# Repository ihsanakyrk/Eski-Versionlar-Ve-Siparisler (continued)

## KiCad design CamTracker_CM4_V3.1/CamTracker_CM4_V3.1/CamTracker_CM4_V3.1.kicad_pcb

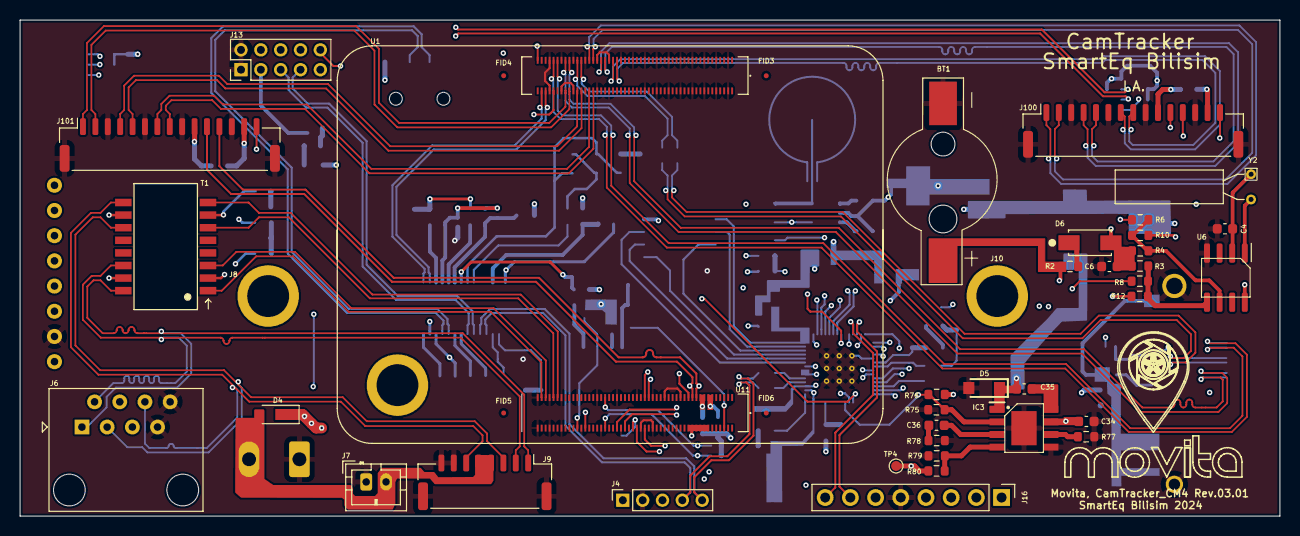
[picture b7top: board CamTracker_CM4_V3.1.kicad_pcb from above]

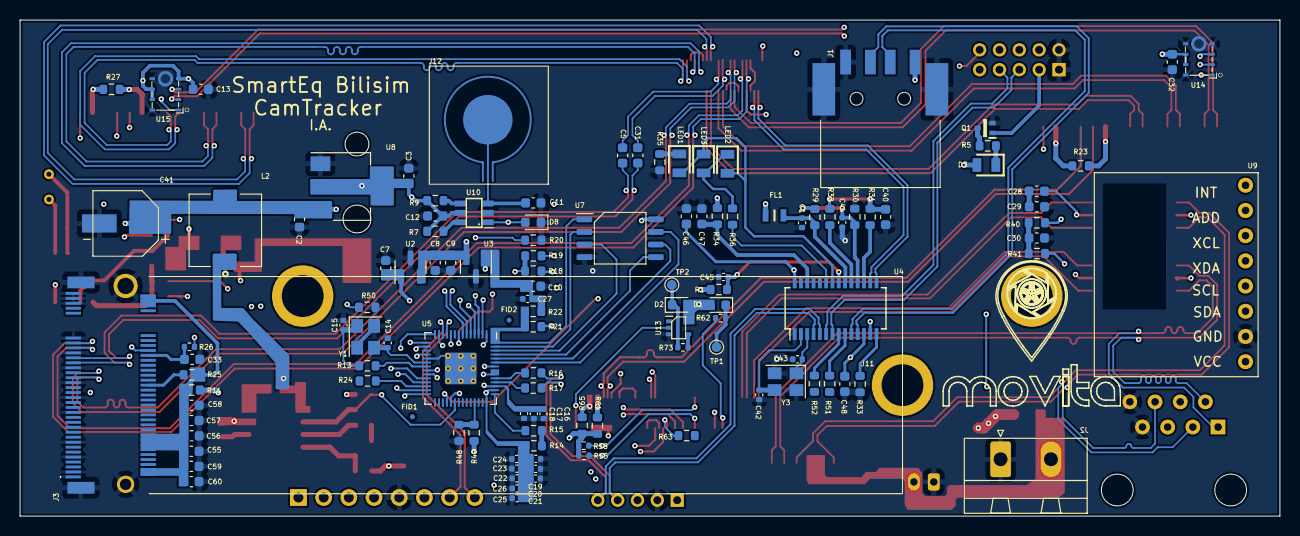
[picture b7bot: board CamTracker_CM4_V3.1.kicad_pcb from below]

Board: 6 copper layers, 127.0 x 50.0 mm, 163 parts (120 on the bottom side), 144 nets.

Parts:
BT1: MYOUNG MY-1220-01; BS-12-B3AA003
C1, C45: 10uF; C_0402_1005Metric
C2, C3, C7, C8, C9, C10, C34, C48: 10uF; C_0603_1608Metric
C4: 22pF; C_0603_1608Metric
C5, C31: 100nF X5R 10V; C_0603_1608Metric
C6, C35: 100nF; C_0603_1608Metric
C11: 30pF; C_0603_1608Metric
C12: 1uF; C_0603_1608Metric
C13, C32, C40, C46, C47, C55, C56, C57, C58, C59, C60: 0.1uF; C_0603_1608Metric
C14, C15, C42, C43: 27pF; C_0402_1005Metric
C16, C17, C20, C21, C22, C23, C24, C25, C26, C27: 100nF; C_0402_1005Metric
C18, C19: 1uF; C_0402_1005Metric
C28, C29: 0.01uF; C_0603_1608Metric
C30: 1000pF; C_0603_1608Metric
C33: 100nF X5R 16V; C_0603_1608Metric
C36: 150pF; C_0603_1608Metric
C41: 100uF; CAPAE660X550N
C44: 0.1uF; C_0402_1005Metric
D1: LED Green; LED_0603_1608Metric
D2: LED Red; LED_0603_1608Metric
D3: LED; LEDC2012X80N
D4: 2SS100L-W; 2SS100LW
D5: SS34FA; SODFL3618X143N
D6: SS14; DIOM4325X250N
D8: LED; LED_0603_1608Metric
FID1, FID2, FID3, FID4, FID5, FID6: Fiducial; Fiducial_0.5mm_Mask1mm
FL1: BLM21BB050SN1D; BLM21BB050SH1D
IC3: MP1584EN; SOIC127P600X170-9N
J1: USB-A Female SMD connector; USB_A_CNCTech_1001-011-01101_Horizontal
J2: DNP; PhoenixContact_MSTBA_2,5_2-G-5,08_1x02_P5.08mm_Horizontal
J3: APCI0079-P002A J8900 M.2 M Key; 121992306
J4: Conn_01x05_Male; PinSocket_1x05_P2.00mm_Vertical
J6: DNP; RJ45_Amphenol_54602-x08_Horizontal
J7: Conn_01x02_Female; JST_PH_B2B-PH-K_1x02_P2.00mm_Vertical
J8, J10: Screw_Terminal_01x01; Screw_terminal_shinbo
J9: JST_GH_BM08B-GHS-TBT_1x08-1MP_P1.25mm_Vertical
J11: M3x*0.5 L=3; Screw_terminal_shinbo
J12: DNP; Touch Pad
J13: MALE Through Hole PinHeader; PinHeader_2x05_P2.00mm_Vertical
J16: DNP; PinHeader_1x08_P2.54mm_Vertical
J100, J101: Conn_01x15_Female; JST_1x15-1MP_P1.25mm_Horizontal
L2: CDRH74NP-100MC-B; CDRH74NP100MCB
LED1, LED2, LED3: 150080VS75000; LEDC2012X80N
Q1: DTC043ZEBTL; SOTFL50P160X85-3N
R1, R7, R9, R10, R12, R19, R22, R50, R51, R52, R65: DNP; R_0603_1608Metric
R2: 150R; R_0603_1608Metric
R3, R4: 4.7K; R_0603_1608Metric
R5, R75: 2.2K; R_0603_1608Metric
R6, R8, R11, R18, R23, R24, R27, R63, R64: 0R; R_0603_1608Metric
R13, R21, R48: 1K; R_0603_1608Metric
R14: 200R; R_0603_1608Metric
R15: 1R; R_0603_1608Metric
R16, R17: 27R; R_0603_1608Metric
R20, R31, R32, R76, R78: 100K; R_0603_1608Metric
R25, R34, R49: 10K; R_0603_1608Metric
R26: 1K 5%; R_0402_1005Metric
R29, R30: 47K; R_0603_1608Metric
R33: 2.7K; R_0603_1608Metric
R35, R36: 470R; R_0603_1608Metric
R40, R41: 75R; R_0603_1608Metric
R55, R58: 2.2K 1%; R_0402_1005Metric
R62, R73: 1K; R_0402_1005Metric
R77: 200K; R_0603_1608Metric
R79: 40.2K; R_0603_1608Metric
R80: 210K; R_0603_1608Metric
T1: H1102NL
TP1, TP2, TP4: TestPoint; TestPoint_Pad_D1.0mm
U1: DF40C-100DS-0.4V; DF40C-100DS-0.4V_CM4_Unit_B
U2, U3: TLV76033DBZT; SOT-23
U4: FE1.1s; SSOP-28_3.9x9.9mm_P0.635mm
U5: RP2040; RP2040-QFN-56
U6: PCF8563T; SOIC-8_3.9x4.9mm_P1.27mm
U7: W25Q128JVS; SOIC-8_5.23x5.23mm_P1.27mm
U8: AMS1117-3.3; SOT-223-3_TabPin2
U9: DNP; module_mpu6050
U10: TTP223
U11: DF40C-100DS-0.4V; DF40C-100DS-0.4V_CM4_Unit_A
U13: 74LVC1G07SE-7; SOT-353_SC-70-5
U14, U15: INMP441
Y1, Y3: Crystal_GND12Mhz; Crystal_SMD_3225-4Pin_3.2x2.5mm
Y2: 32.768 KHz; Crystal_AT310_D3.0mm_L10.0mm_Horizontal

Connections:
3.3V_HUB: C40.1, C45.2, R1.1, R31.2, R32.2, U4.13 (VD33), U4.21 (VD33_O)
5V_A: C1.2, FL1.2, R29.2, U4.20 (VDD5)
+1V1: C16.1, C17.1, C18.1, U5.23 (DVDD), U5.45 (VREG_VOUT), U5.50 (DVDD)
/CM4/+1.8v: R65.1, U11.88 (+1.8v_(Output)), U11.90 (+1.8v_(Output))
/CM4/+5v: C2.2, C41.1, D3.2 (A), FL1.1, J1.1 (VBUS), L2.2, R34.2, R80.2, TP4.1, U8.3 (VI), U11.77 (+5v_(Input)), U11.79 (+5v_(Input)), U11.81 (+5v_(Input)), U11.83 (+5v_(Input)), U11.85 (+5v_(Input)), U11.87 (+5v_(Input))
/CM4/CAM0_C_N: J100.7, U1.140 (CAM0_C_N)
/CM4/CAM0_C_P: J100.8, U1.142 (CAM0_C_P)
/CM4/CAM0_D0_N: J100.1, U1.128 (CAM0_D0_N)
/CM4/CAM0_D0_P: J100.2, U1.130 (CAM0_D0_P)
/CM4/CAM0_D1_N: J100.4, U1.134 (CAM0_D1_N)
/CM4/CAM0_D1_P: J100.5, U1.136 (CAM0_D1_P)
/CM4/CAM1_C_N: J101.7, U1.127 (CAM1_C_N)
/CM4/CAM1_C_P: J101.8, U1.129 (CAM1_C_P)
/CM4/CAM1_D0_N: J101.1, U1.115 (CAM1_D0_N)
/CM4/CAM1_D0_P: J101.2, U1.117 (CAM1_D0_P)
/CM4/CAM1_D1_N: J101.4, U1.121 (CAM1_D1_N)
/CM4/CAM1_D1_P: J101.5, U1.123 (CAM1_D1_P)
/CM4/CM4_+3.3v: D1.2 (A), D2.2 (A), J100.14, J101.14, R23.1, R27.1, R64.1, U11.84 (+3.3v_(Output)), U11.86 (+3.3v_(Output)), U13.5 (VCC)
/CM4/CM4_PCF_SCL: R4.2, R6.1, R10.1, U6.6 (SCL)
/CM4/CM4_PCF_SDA: R3.2, R8.1, R12.1, U6.5 (SDA)
/CM4/GPIO2: R8.2, U11.58 (GPIO2)
/CM4/GPIO3: R6.2, U11.56 (GPIO3)
/CM4/GPIO14: U5.28 (GPIO17), U11.55 (GPIO14)
/CM4/GPIO15: U5.27 (GPIO16), U11.51 (GPIO15)
/CM4/GPIO18: R63.1, U11.49 (GPIO18)
/CM4/GPIO21: J100.15, J101.15, U11.25 (GPIO21)
/CM4/GPIO24: U5.25 (SWD), U11.45 (GPIO24)
/CM4/GPIO25: U5.24 (SWCLK), U11.41 (GPIO25)
/CM4/GPIO_VREF: R55.1, R58.1, R64.2, R65.2, U11.78 (GPIO_VREF(1.8v/3.3v_Input))
/CM4/ID_SC: J100.11, R55.2, U11.35 (ID_SC)
/CM4/ID_SD: J100.12, R58.2, U11.36 (ID_SD)
/CM4/PCIE_CLK_N: J3.53, U1.112 (PCIe_CLK_N)
/CM4/PCIE_CLK_P: J3.55, U1.110 (PCIe_CLK_P)
/CM4/PCIE_CLK_nREQ: J3.52, U1.102 (PCIe_CLK_nREQ)
/CM4/PCIE_RX_N: J3.41, U1.118 (PCIe_RX_N)
/CM4/PCIE_RX_P: J3.43, U1.116 (PCIe_RX_P)
/CM4/PCIE_TX_N: C5.2, U1.124 (PCIe_TX_N)
/CM4/PCIE_TX_P: C31.2, U1.122 (PCIe_TX_P)
/CM4/PCIE_nRST: R26.2, U1.109 (PCIe_nRST)
/CM4/SCL0: J101.11, R10.2, U11.80 (SCL0)
/CM4/SDA0: J101.12, R12.2, U11.82 (SDA0)
/CM4/USB2_N: U1.103 (USB2_N), U4.15 (DMU)
/CM4/USB2_P: U1.105 (USB2_P), U4.16 (DPU)
/CM4/nPWR_LED: U11.95 (nPI_LED_PWR), U13.2
/I2C/3V3_Sensor: C6.1, C7.2, D6.2, R3.1, R4.1, U2.1 (OUT), U9.1 (VCC)
/I2C/SCL_RP2040: R18.1, U9.3 (SCL)
/INMP441/+3.3V: C3.2, C12.1, C13.1, C32.1, R1.2, R7.1, R9.1, R11.1, U8.2 (VO), U10.5 (VDD), U14.7 (VDD), U14.8 (CHIEN), U15.4 (L/R), U15.7 (VDD), U15.8 (CHIEN)
/INMP441/SCK: R19.1, U14.1 (SCK), U15.1 (SCK)
/PCIE/3.3V_XL: C55.1, C56.1, C57.1, C58.1, C59.1, C60.1, J3.2, J3.4, J3.12, J3.14, J3.16, J3.18, J3.70, J3.72, J3.74, R11.2, R25.2
/PCIE/TX_N: C5.1, J3.47
/PCIE/TX_P: C31.1, J3.49
/Power Unit/+3V3: C10.2, C19.1, C20.1, C21.1, C22.1, C23.1, C24.1, C25.1, C26.1, C27.1, J16.6, R14.1, R22.1, U3.1 (OUT), U5.1 (IOVDD), U5.10 (IOVDD), U5.22 (IOVDD), U5.33 (IOVDD), U5.42 (IOVDD), U5.44 (VREG_IN), U5.48 (USB_VDD), U5.49 (IOVDD), U7.8 (VCC)
/RP2040/GPIO0: U5.2 (GPIO0), U9.4 (SDA)
/RP2040/GPIO1: R18.2, R19.2, U5.3 (GPIO1)
/RP2040/GPIO2: R20.1, U5.4 (GPIO2), U14.2 (SD), U15.2 (SD)
/RP2040/GPIO3: U5.5 (GPIO3), U14.3 (WS), U15.3 (WS)
/RP2040/GPIO4_TX: J13.10, U5.6 (GPIO4)
/RP2040/GPIO5_RX: J13.9, U5.7 (GPIO5)
/RP2040/GPIO6: D8.2 (A), U5.8 (GPIO6), U10.1 (Q)
/RP2040/GPIO15: R50.1, U5.18 (GPIO15)
/RP2040/GPIO21: J13.6, U5.32 (GPIO21)
/RP2040/GPIO22: IC3.2 (EN), R75.1, R76.2, U5.34 (GPIO22)
/RP2040/GPIO27_ADC1: R48.1, R49.2, U5.39 (GPIO27_ADC1)
/RP2040/QSPI_SCLK: U5.52 (QSPI_SCLK), U7.6 (CLK)
/RP2040/QSPI_SD0: U5.53 (QSPI_SD0), U7.5 (DI(IO0))
/RP2040/QSPI_SD1: U5.55 (QSPI_SD1), U7.2 (DO(IO1))
/RP2040/QSPI_SD2: U5.54 (QSPI_SD2), U7.3 (IO2)
/RP2040/QSPI_SD3: U5.51 (QSPI_SD3), U7.7 (IO3)
/RP2040/QSPI_SS: R21.1, R22.2, U5.56 (QSPI_SS), U7.1 (~CS)
/RP2040/USB_RP2040_D+: J4.5, R16.1, U4.5 (DP4)
/RP2040/USB_RP2040_D-: J4.4, R17.1, U4.4 (DM4)
/RP2040/XIN: C14.1, U5.20 (XIN), Y1.3
/RP2040/XOUT: R13.1, U5.21 (XOUT)
/RP2040/~USB_BOOT: J4.3, R21.2
/TopBoard_Connection/USB_GSM_D+: J13.5, U4.7 (DP3)
/TopBoard_Connection/USB_GSM_D-: J13.7, U4.6 (DM3)
ADC_VREF: R14.2, R15.1
DRV1: LED1.2, LED2.2, LED3.1, U4.22 (DRV)
GND: BT1.2 (-), C1.1, C2.1, C3.1, C4.2, C6.2, C7.1, C8.1, C9.1, C10.1, C11.2, C12.2, C13.2, C14.2, C15.2, C16.2, C17.2, C18.2, C19.2, C20.2, C21.2, C22.2, C23.2, C24.2, C25.2, C26.2, C27.2, C29.2, C30.2, C32.2, C33.1, C34.1, C40.2, C41.2, C42.2, C43.2, C44.2, C45.1, C46.2, C47.2, C48.2, C55.2, C56.2, C57.2, C58.2, C59.2, C60.2, D5.2, D8.1 (K), IC3.5 (GND), IC3.9 (EP), J1.4 (GND), J1.5 (Shield), J2.1, J3.1, J3.3, J3.9, J3.15, J3.21, J3.27, J3.33, J3.39, J3.45, J3.51, J3.57, J3.71, J3.73, J3.75, J3.MH1, J3.MH2, J3.MP1, J3.MP2, J4.2, J6.7, J6.8, J7.1, J9.7, J9.8, J9.MP, J13.1, J13.2, J16.5, J100.3, J100.6, J100.9, J100.13, J101.3, J101.6, J101.9, J101.13, Q1.2, R20.2, R30.2, R33.2, R35.2, R48.2, R50.2, R75.2, R77.2, R78.2, R79.2, U1.107 (GND), U1.108 (GND), U1.113 (GND), U1.114 (GND), U1.119 (GND), U1.120 (GND), U1.125 (GND), U1.126 (GND), U1.131 (GND), U1.132 (GND), U1.137 (GND), U1.138 (GND), U1.144 (GND), U1.150 (GND), U1.155 (GND), U1.156 (GND), U1.161 (GND), U1.162 (GND), U1.167 (GND), U1.168 (GND), U1.173 (GND), U1.174 (GND), U1.179 (GND), U1.180 (GND), U1.185 (GND), U1.186 (GND), U1.191 (GND), U1.192 (GND), U1.197 (GND), U1.198 (GND), U2.3 (GND), U3.3 (GND), U4.1 (VSS), U5.19 (TESTEN), U5.57 (GND), U6.4 (VSS), U7.4 (GND), U8.1 (GND), U9.2 (GND), U10.2 (VSS), U11.1 (GND), U11.2 (GND), U11.7 (GND), U11.8 (GND), U11.13 (GND), U11.14 (GND), U11.22 (GND), U11.23 (GND), U11.32 (GND), U11.33 (GND), U11.42 (GND), U11.43 (GND), U11.52 (GND), U11.53 (GND), U11.59 (GND), U11.60 (GND), U11.65 (GND), U11.66 (GND), U11.71 (GND), U11.74 (GND), U11.98 (GND), U13.3 (GND), U14.4 (L/R), U14.5 (GND), U14.6 (GND), U14.9 (GND), U15.5 (GND), U15.6 (GND), U15.9 (GND), Y1.2, Y1.4, Y3.2, Y3.4
LED1: R36.2, U4.23 (LED1/EESCL)
unnamed: BT1.1 (+), R2.2, U6.8 (VDD)
unnamed: C15.1, R13.2, Y1.1
unnamed: C28.2, C29.1
unnamed: C30.1, R40.1, R41.1
unnamed: C33.2, J3.50, R26.1
unnamed: C36.1, R78.1
unnamed: D1.1 (K), R62.1, TP1.1
unnamed: D2.1 (K), R73.1, TP2.1
unnamed: D3.1 (K), R5.1
unnamed: D6.1, R2.1
unnamed: C35.2, IC3.8 (BST)
unnamed: C36.2, IC3.3 (COMP)
unnamed: IC3.4 (FB), R79.1, R80.1
unnamed: IC3.6 (FREQ), R77.1
unnamed: C35.1, D5.1, IC3.1 (SW), L2.1
unnamed: J3.38, R25.1
unnamed: J13.3, Q1.1
unnamed: J100.10, R27.2
unnamed: J101.10, R23.2
unnamed: LED1.1, R35.1
unnamed: LED2.1, LED3.2, R36.1
unnamed: Q1.3, R5.2
unnamed: R73.2, U13.4
unnamed: C28.1, T1.2 (CT1), T1.7 (CT2)
unnamed: R40.2, T1.10 (CT3)
unnamed: R41.2, T1.15 (CT4)
unnamed: R32.1, U4.19 (BUSJ)
unnamed: R52.2, U4.8 (DM2)
unnamed: R51.2, U4.9 (DP2)
unnamed: R33.1, U4.14 (REXT)
unnamed: C44.1, R29.1, R30.1, U4.18 (VBUSM)
unnamed: C46.1, C48.1, U4.12 (VD18_O), U4.28 (VD18)
unnamed: C43.1, U4.3 (XIN), Y3.1
unnamed: C42.1, U4.2 (XOUT), Y3.3
unnamed: R31.1, U4.17 (~XRSTJ)
unnamed: R15.2, U5.43 (ADC_AVDD)
unnamed: R24.1, U5.26 (RUN)
unnamed: R17.2, U5.46 (USB_DM)
unnamed: R16.2, U5.47 (USB_DP)
unnamed: U6.1 (OSCI), Y2.2
unnamed: C4.1, U6.2 (OSCO), Y2.1
unnamed: R9.2, U10.4 (AHLB)
unnamed: C11.1, J12.1, U10.3 (I)
unnamed: R7.2, U10.6 (TOG)
unnamed: R62.2, U11.21 (PI_nLED_Activity)
OVCJ: C47.1, R34.1, U4.26 (OVCJ)
RX_N: T1.8 (RD-), U11.12 (Ethernet_Pair0_P)
RX_P: T1.6 (RD+), U11.10 (Ethernet_Pair0_N)
SCL_9: J16.7, U5.12 (GPIO9)
SDA_8: J16.8, U5.11 (GPIO8)
SPI_CS_13: J16.1, U5.16 (GPIO13)
SPI_RX_12: J16.2, U5.15 (GPIO12)
SPI_SCK_10: J16.4, U5.13 (GPIO10)
SPI_TX_11: J16.3, U5.14 (GPIO11)
TRD0_N: J6.2, J9.2, T1.14 (TX-)
TRD0_P: J6.1, J9.1, T1.16 (TX+)
TRD1_N: J6.6, J9.6, T1.9 (RX-)
TRD1_P: J6.3, J9.3, T1.11 (RX+)
TX_N: T1.3 (TD-), U11.6 (Ethernet_Pair1_N)
TX_P: T1.1 (TD+), U11.4 (Ethernet_Pair1_P)
USB_CON_A_D+: J1.3 (D+), U4.11 (DP1)
USB_CON_A_D-: J1.2 (D-), U4.10 (DM1)
VIN: C8.2, C9.2, C34.2, D4.1, IC3.7 (VIN), J4.1, J13.4, J13.8, R49.1, R76.1, U2.2 (IN), U3.2 (IN)
VRAW: D4.2, J2.2, J6.4, J6.5, J7.2, J9.4, J9.5

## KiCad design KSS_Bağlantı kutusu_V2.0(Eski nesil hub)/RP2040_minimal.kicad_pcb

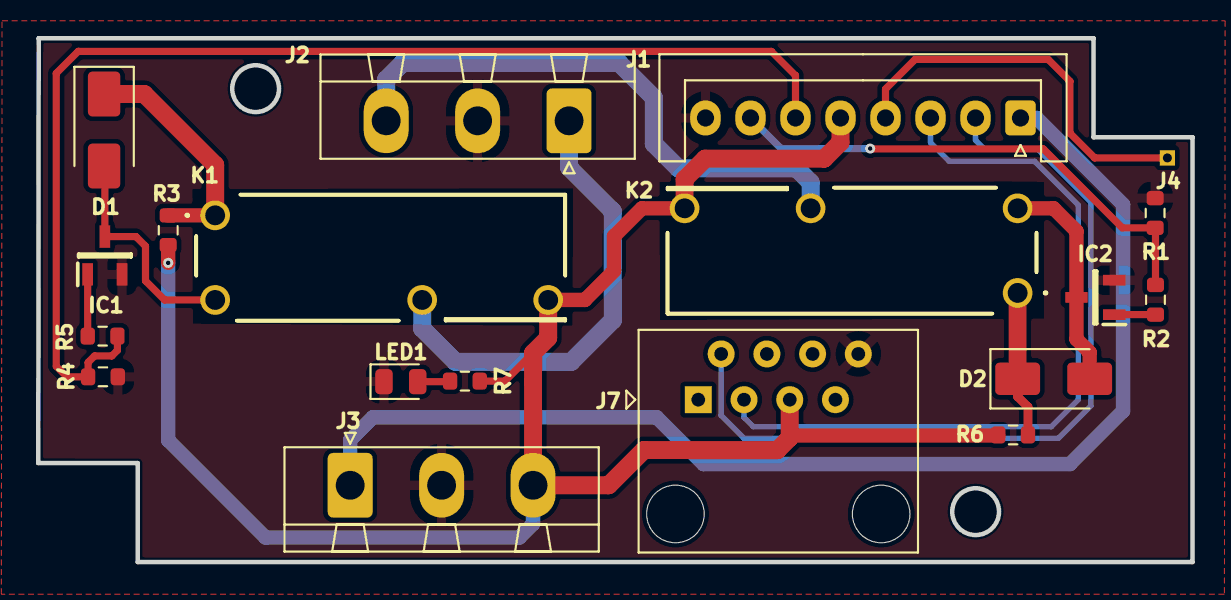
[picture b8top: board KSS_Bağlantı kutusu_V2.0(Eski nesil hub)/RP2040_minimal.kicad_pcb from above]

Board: 2 copper layers, 64.1 x 29.1 mm, 19 parts (0 on the bottom side), 17 nets.

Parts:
D1, D2: MRA4007T3G; D_SMA
IC1, IC2: MMBT2222ALT1G; SOT96P237X111-3N
J1: Conn_01x08_Socket; JST_XH_S8B-XH-A_1x08_P2.50mm_Horizontal
J2, J3: Conn_01x03_Pin; KF2EDGR-Y-5.08-03P-1 B
J4: DNP; PinHeader_1x01_P1.00mm_Horizontal
J7: 8P8C; RJ45_Amphenol_54602-x08_Horizontal
K1, K2: HF46F5HS1
LED1: NCD0805R1; LED_0805_2012Metric
R1, R2, R4, R5: 10K; R_0603_1608Metric
R3, R6: 0R; R_0603_1608Metric
R7: 3.3K; R_0603_1608Metric

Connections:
/Flash: J2.3, K2.3
/GPIO6: J1.6, R4.2, R5.2
/GPIO7: J1.7, R1.2, R2.2
/GPIO19: J1.4, J4.1
/HORN: J2.1, K1.3
/IGN: J1.1, J3.1
GND: IC1.2 (E), IC2.2 (E), J1.8, J2.2, J3.2, J7.8, LED1.1, R1.1, R4.1
unnamed: D1.2 (A), IC1.3 (C), K1.2
unnamed: D1.1 (K), K1.1, R3.1
unnamed: D2.2 (A), IC2.3 (C), K2.2
unnamed: D2.1 (K), K2.1, R6.1
unnamed: IC1.1 (B), R5.1
unnamed: IC2.1 (B), R2.1
unnamed: LED1.2, R7.2
RS485_A: J1.3, J7.3
RS485_B: J1.2, J7.2
VBUS: J1.5, J3.3, J7.5, K1.4, K2.4, R3.2, R6.2, R7.1

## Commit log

2025-09-01 ilk yükleme
2025-09-02 GSM güncellendi
